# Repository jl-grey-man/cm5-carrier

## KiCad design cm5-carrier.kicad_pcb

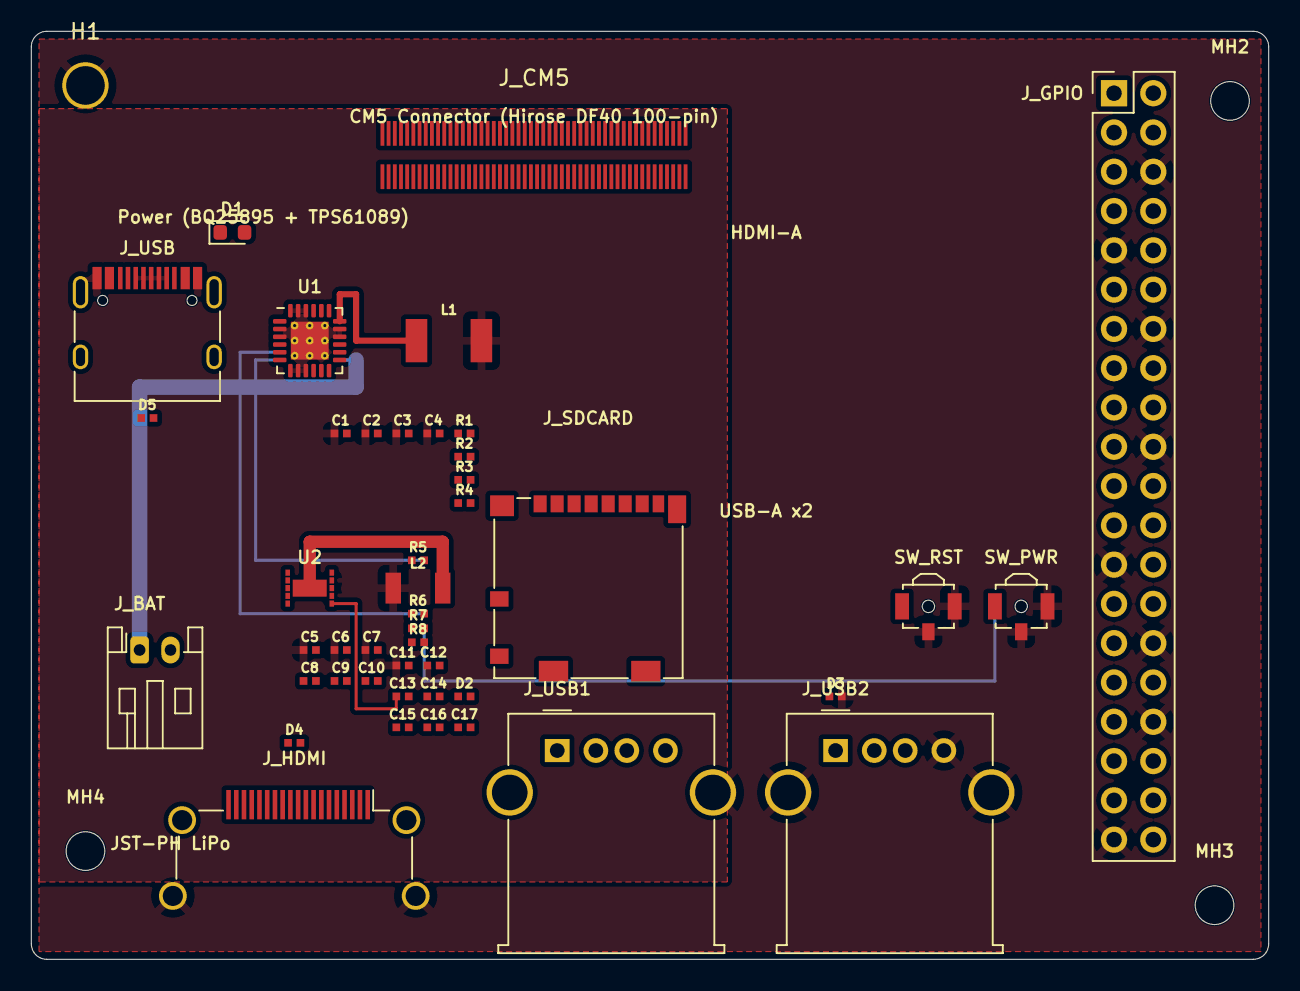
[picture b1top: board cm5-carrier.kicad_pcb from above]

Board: 4 copper layers, 80.0 x 60.0 mm, 48 parts (0 on the bottom side), 52 nets.

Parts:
C1: 10uF/10V; SMD_C1_GENERATED
C2: 100nF; SMD_C2_GENERATED
C3: 10uF; SMD_C3_GENERATED
C4: 10uF/10V; SMD_C4_GENERATED
C5: 100nF; SMD_C5_GENERATED
C6: 100nF; SMD_C6_GENERATED
C7: 47uF; SMD_C7_GENERATED
C8: 47uF/10V; SMD_C8_GENERATED
C9: 100uF/6.3V; SMD_C9_GENERATED
C10: 47uF/10V; SMD_C10_GENERATED
C11: 47uF/10V; SMD_C11_GENERATED
C12: 100nF/10V; SMD_C12_GENERATED
C13: 100nF/10V; SMD_C13_GENERATED
C14: 47uF/10V; SMD_C14_GENERATED
C15: 47uF/10V; SMD_C15_GENERATED
C16: 47uF/10V; SMD_C16_GENERATED
C17: 100nF/10V; SMD_C17_GENERATED
D1: LED_PWR; LED_0603_1608Metric
D2, D3, D4, D5: TVS_5V; ESD_TVS_0402_GENERATED
H1: M2.5; MountingHole_2.5mm_M2.5
J_BAT: LiPo JST-PH; JST_PH_S2B-PH-K_1x02_P2.00mm_Horizontal
J_CM5: DF40HC(3.0)-100DS-0.4V; Hirose_DF40HC-100DS-0.4V_GENERATED
J_GPIO: GPIO_2x20; PinHeader_2x20_P2.54mm_Vertical
J_HDMI: HDMI-A; HDMI_A_Amphenol_10029449-x01xLF_Horizontal
J_SDCARD: microSD; microSD_HC_Molex_104031-0811
J_USB: USB-C 5V Input; USB_C_Receptacle_HRO_TYPE-C-31-M-12
J_USB1, J_USB2: USB-A; USB_A_Molex_67643_Horizontal
L1: 2.2uH/8A; SMD_L1_GENERATED
L2: 1.0uH/10A; SMD_L2_GENERATED
MH2, MH3, MH4: M2.5; MountingHole_2.5mm_M2.5
R1: 100k; SMD_R1_GENERATED
R2: 10k; SMD_R2_GENERATED
R3: 10k; SMD_R3_GENERATED
R4: 4.7k; SMD_R4_GENERATED
R5: 10k; SMD_R5_GENERATED
R6: 10k; SMD_R6_GENERATED
R7: 10k; SMD_R7_GENERATED
R8: 10k; SMD_R8_GENERATED
SW_PWR: POWER; SW_SPST_B3U-3100P-B
SW_RST: RESET; SW_SPST_B3U-3100P-B
U1: BQ25895RTW; WQFN-24-1EP_4x4mm_P0.5mm
U2: TPS61089; TPS61089_VSON-10_3x2mm_GENERATED

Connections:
+3.3V: J_CM5.1, J_CM5.2, J_CM5.7, J_CM5.8, J_CM5.13, J_CM5.14, J_CM5.22, J_CM5.23, J_CM5.32, J_CM5.33, J_CM5.42, J_CM5.43, J_CM5.52, J_CM5.53, J_CM5.59, J_CM5.60, J_CM5.65, J_CM5.66, J_CM5.71, J_CM5.74, J_CM5.98, J_GPIO.1, J_GPIO.17, J_SDCARD.4, R5.1, R6.1, R7.1, R8.1
+5V_CM5: C8.1, C9.1, C10.1, C14.1, C15.1, C16.1, C17.1, D2.1, D3.1, D4.1, J_CM5.77, J_CM5.79, J_CM5.81, J_CM5.83, J_CM5.85, J_CM5.87, J_GPIO.2, J_GPIO.4, J_HDMI.18, J_USB1.1, J_USB2.1, U2.2, U2.6
/CM5 Connector/1V8_CM4: J_CM5.88, J_CM5.90
/CM5 Connector/3V3_CM4: J_CM5.84, J_CM5.86
/CM5 Connector/GLOBAL_EN: J_CM5.99, SW_RST.1
/CM5 Connector/GPIO2: J_CM5.58, J_GPIO.3
/CM5 Connector/GPIO3: J_CM5.56, J_GPIO.5
/CM5 Connector/GPIO4: J_CM5.54, J_GPIO.7
/CM5 Connector/GPIO5: J_CM5.34, J_GPIO.29
/CM5 Connector/GPIO6: J_CM5.30, J_GPIO.31
/CM5 Connector/GPIO7: J_CM5.37, J_GPIO.26
/CM5 Connector/GPIO8: J_CM5.39, J_GPIO.24
/CM5 Connector/GPIO9: J_CM5.40, J_GPIO.21
/CM5 Connector/GPIO10: J_CM5.44, J_GPIO.19
/CM5 Connector/GPIO11: J_CM5.38, J_GPIO.23
/CM5 Connector/GPIO12: J_CM5.31, J_GPIO.32
/CM5 Connector/GPIO13: J_CM5.28, J_GPIO.33
/CM5 Connector/GPIO14: J_CM5.55, J_GPIO.8
/CM5 Connector/GPIO15: J_CM5.51, J_GPIO.10
/CM5 Connector/GPIO16: J_CM5.29, J_GPIO.36
/CM5 Connector/GPIO17: J_CM5.50, J_GPIO.11
/CM5 Connector/GPIO18: J_CM5.49, J_GPIO.12
/CM5 Connector/GPIO19: J_CM5.26, J_GPIO.35
/CM5 Connector/GPIO20: J_CM5.27, J_GPIO.38
/CM5 Connector/GPIO21: J_CM5.25, J_GPIO.40
/CM5 Connector/GPIO22: J_CM5.46, J_GPIO.15
/CM5 Connector/GPIO23: J_CM5.47, J_GPIO.16
/CM5 Connector/GPIO24: J_CM5.45, J_GPIO.18
/CM5 Connector/GPIO25: J_CM5.41, J_GPIO.22
/CM5 Connector/GPIO26: J_CM5.24, J_GPIO.37
/CM5 Connector/GPIO27: J_CM5.48, J_GPIO.13
/CM5 Connector/ID_SC: J_CM5.35, J_GPIO.28
/CM5 Connector/ID_SD: J_CM5.36, J_GPIO.27
/CM5 Connector/SD_CLK: J_CM5.57, J_SDCARD.5
/CM5 Connector/SD_CMD: J_CM5.62, J_SDCARD.3
/CM5 Connector/SD_DAT0: J_CM5.63, J_SDCARD.7
/CM5 Connector/SD_DAT1: J_CM5.67, J_SDCARD.8
/CM5 Connector/SD_DAT2: J_CM5.69, J_SDCARD.1
/CM5 Connector/SD_DAT3: J_CM5.61, J_SDCARD.2
/PWR_BUT_BTN: J_CM5.92, R7.2, SW_PWR.1, U1.12
GND: C1.2, C2.2, C3.2, C4.2, C5.2, C6.2, C7.2, C8.2, C9.2, C10.2, C11.2, C12.2, C14.2, C15.2, C16.2, C17.2, D2.2, D3.2, D4.2, D5.2, J_BAT.2, J_GPIO.6, J_GPIO.9, J_GPIO.14, J_GPIO.20, J_GPIO.25, J_GPIO.30, J_GPIO.34, J_GPIO.39, J_HDMI.2, J_HDMI.5, J_HDMI.8, J_HDMI.11, J_HDMI.17, J_HDMI.SH, J_SDCARD.6, J_SDCARD.9, J_SDCARD.10, J_SDCARD.11, J_USB.A1, J_USB.A6, J_USB.A7, J_USB.A8, J_USB.A12, J_USB.B1, J_USB.B6, J_USB.B7, J_USB.B8, J_USB.B12, J_USB.S1, J_USB1.4, J_USB1.5, J_USB2.4, J_USB2.5, R1.2, R2.2, R3.2, R4.2, R8.2, SW_PWR.2, SW_PWR.3, SW_RST.2, SW_RST.3, U1.2, U1.3, U1.7, U1.8, U1.9, U1.11, U1.14, U1.16, U1.17, U1.22, U1.23, U1.24, U1.25, U2.5
I2C0_SCL: J_CM5.80, R6.2, U1.5
I2C0_SDA: J_CM5.82, R5.2, U1.6
Net-U1-SW: L1.1, R4.1, U1.18, U1.19, U1.20, U1.21
Net-U2-BOOT: C13.1, U2.10
Net-U2-COMP: R3.1, U2.4
Net-U2-FB: R2.1, U2.3
Net-U2-ILIM: R1.1, U2.8
Net-U2-SW: C13.2, L2.2, U2.11
VBATT: J_BAT.1, U1.13
VBUS: D1.1, D1.2, D5.1, J_USB.A4, J_USB.A5, J_USB.A9, J_USB.B4, J_USB.B5, J_USB.B9, U1.1
VSYS: C1.1, C2.1, C3.1, C4.1, C5.1, C6.1, C7.1, C11.1, C12.1, L1.2, L2.1, U1.15, U2.7, U2.9

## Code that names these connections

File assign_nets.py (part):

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_C = '/CM5 Connector/'
GPIO_HEADER = {
    1:  '+3.3V',          2:  '+5V_CM5',
    3:  _C+'GPIO2',       4:  '+5V_CM5',
    5:  _C+'GPIO3',       6:  'GND',
    7:  _C+'GPIO4',       8:  _C+'GPIO14',
    9:  'GND',            10: _C+'GPIO15',
    11: _C+'GPIO17',      12: _C+'GPIO18',
    13: _C+'GPIO27',      14: 'GND',
    15: _C+'GPIO22',      16: _C+'GPIO23',
    17: '+3.3V',          18: _C+'GPIO24',
    19: _C+'GPIO10',      20: 'GND',
    21: _C+'GPIO9',       22: _C+'GPIO25',
    23: _C+'GPIO11',      24: _C+'GPIO8',
    25: 'GND',            26: _C+'GPIO7',
    27: _C+'ID_SD',       28: _C+'ID_SC',
    29: _C+'GPIO5',       30: 'GND',
    31: _C+'GPIO6',       32: _C+'GPIO12',
    33: _C+'GPIO13',      34: 'GND',
    35: _C+'GPIO19',      36: _C+'GPIO16',
    37: _C+'GPIO26',      38: _C+'GPIO20',
    39: 'GND',            40: _C+'GPIO21',
}

# ── HDMI-A connector (Amphenol 10029449) ──────────────────────────────
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
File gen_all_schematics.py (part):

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
Signal mapping (global labels used in power.kicad_sch → hierarchical in other sheets):
  +5V_CM5  → connects to CM5 sheet "+5V" pin
  I2C0_SDA → connects to CM5 sheet "SDA0" pin
  I2C0_SCL → connects to CM5 sheet "SCL0" pin
  VBUS     → connects to USB sheet "5V" pin
"""

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
# ─── Auto-discovered hierarchical labels from each sub-sheet ──────────────────
# CM5:  ['+5V', '1V8_CM4', '3V3_CM4', 'CC1', 'CC2', 'EEPROM_nWP',
#         'ETH_PI{ETH}', 'ETH_nLED_ACTIVITY', 'GLOBAL_EN', 'GPIO4..7',
#         'GPIO_VREF', 'HDMI_PI{HDMI}', 'ID_SC', 'ID_SD', 'PI_nLED_PWR',
#         'PWM', 'PWR_BUT', 'SCL0', 'SDA0', 'TACHO', 'USB2P{USB}',
#         'USBOTG_ID', 'USB_PI{USB}', 'VBUS_EN', 'nLED_ACTIVITY',
#         'nLED_SPEED_100_1000']
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    ("USB_PI{USB}",      "output",        "right", 20.32),
    ("VBUS_EN",          "output",        "right", 27.94),
    ("ETH_PI{ETH}",      "output",        "right", 35.56),
    ("GPIO4",            "bidirectional", "right", 43.18),
    ("GPIO5",            "bidirectional", "right", 48.26),
    ("GPIO6",            "bidirectional", "right", 53.34),
    ("GPIO7",            "bidirectional", "right", 58.42),
    ("TACHO",            "input",         "right", 66.04),
    ("PWM",              "output",        "right", 71.12),
]
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    elements.append(wire(CM5_X - 20, CM5_Y + oy, CM5_X, CM5_Y + oy))

# Power → I2C to CM5
elements.append(global_label("I2C0_SDA", CM5_X - 20, CM5_Y + 40.64, angle=180, shape="bidirectional"))
elements.append(wire(CM5_X - 20, CM5_Y + 40.64, CM5_X, CM5_Y + 40.64))
elements.append(global_label("I2C0_SCL", CM5_X - 20, CM5_Y + 45.72, angle=180, shape="bidirectional"))
elements.append(wire(CM5_X - 20, CM5_Y + 45.72, CM5_X, CM5_Y + 45.72))

# CM5 HDMI_PI → HDMI sheet HDMI_C (wire between sheet boxes)
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elements.append(wire(IO_X - 15, IO_Y + 10.16, IO_X, IO_Y + 10.16))

# IO PWR_BUT → CM5 PWR_BUT (global label bridge)
elements.append(net_label("PWR_BUT_BTN", IO_X + 70 + 5, IO_Y + 17.78))
elements.append(wire(IO_X + 70, IO_Y + 17.78, IO_X + 70 + 5, IO_Y + 17.78))
elements.append(net_label("PWR_BUT_BTN", CM5_X - 5, CM5_Y + 66.04))
elements.append(wire(CM5_X - 5, CM5_Y + 66.04, CM5_X, CM5_Y + 66.04))

# Title / notes
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
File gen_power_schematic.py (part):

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parts.append(placed_sym("power:GND", "GND", "GND", 63, 118))

# I2C to CM5 (global labels for cross-sheet connection)
labels_list.append(global_label("I2C0_SDA", 75, 118, angle=0, shape="bidirectional"))
labels_list.append(global_label("I2C0_SCL", 75, 125, angle=0, shape="bidirectional"))

# SYS output decoupling (2x 47uF)
parts.append(placed_sym("Device:C", "C7", "47uF/10V", 138, 82, footprint=C1210))
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parts.append(placed_sym("power:GND", "GND", "GND", 148, 92))

# SYS → boost stage
labels_list.append(global_label("VSYS", 160, 75, angle=0, shape="output"))

# BAT pins ← JST connector
labels_list.append(global_label("VBATT", 75, 132, angle=0, shape="bidirectional"))
# BAT decoupling (100uF)
parts.append(placed_sym("Device:C", "C9", "100uF/6.3V", 138, 100, footprint=C1210))
parts.append(placed_sym("power:GND", "GND", "GND", 138, 110))
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parts.append(placed_sym("Connector_Generic:Conn_01x02", "J2", "BATT_JST-PH_3.7V",
                          35, 170, footprint=JST_FP,
                          datasheet="https://www.jst-mfg.com/product/detail_e.php?series=199"))
labels_list.append(global_label("VBATT", 55, 167.5, angle=0, shape="output"))
wires_list.append(wire(42, 167.5, 55, 167.5))
parts.append(placed_sym("power:GND", "GND", "GND", 42, 178))
wires_list.append(wire(42, 172.5, 42, 178))
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                          datasheet="https://www.ti.com/lit/ds/symlink/tps61089.pdf"))

# VIN from VSYS
labels_list.append(global_label("VSYS", 195, 68, angle=0, shape="input"))
wires_list.append(wire(200, 68, 230, 68))

# VIN decoupling (2x 47uF + 100nF)
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# Pin 2 (top) = y-3.81 = 81.19, Pin 1 (bottom) = y+3.81 = 88.81
parts.append(placed_sym("Device:R", "R7", "10k", 215, 85, footprint=R))
parts.append(placed_sym("power:+3.3V", "+3.3V", "+3.3V", 215, 81.19))
labels_list.append(global_label("/PWR_BUT_BTN", 215, 88.81, angle=270, shape="bidirectional"))

# R8: +3.3V pull-down (10k, +3.3V → GND)
# Pin 2 (top) = y-3.81 = 91.19, Pin 1 (bottom) = y+3.81 = 98.81
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		(company "Jens Lennartsson")
		(comment 1 "USB-C 5V → BQ25895RTW charger → LiPo (JST-PH 2mm)")
		(comment 2 "LiPo 3.7V → TPS61089 boost → +5V_CM5 (5.1V/5A)")
		(comment 3 "I2C control of charger via CM5 GPIO (I2C0_SDA/SCL)")
	)
	(lib_symbols
		{lib_symbols_str}
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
